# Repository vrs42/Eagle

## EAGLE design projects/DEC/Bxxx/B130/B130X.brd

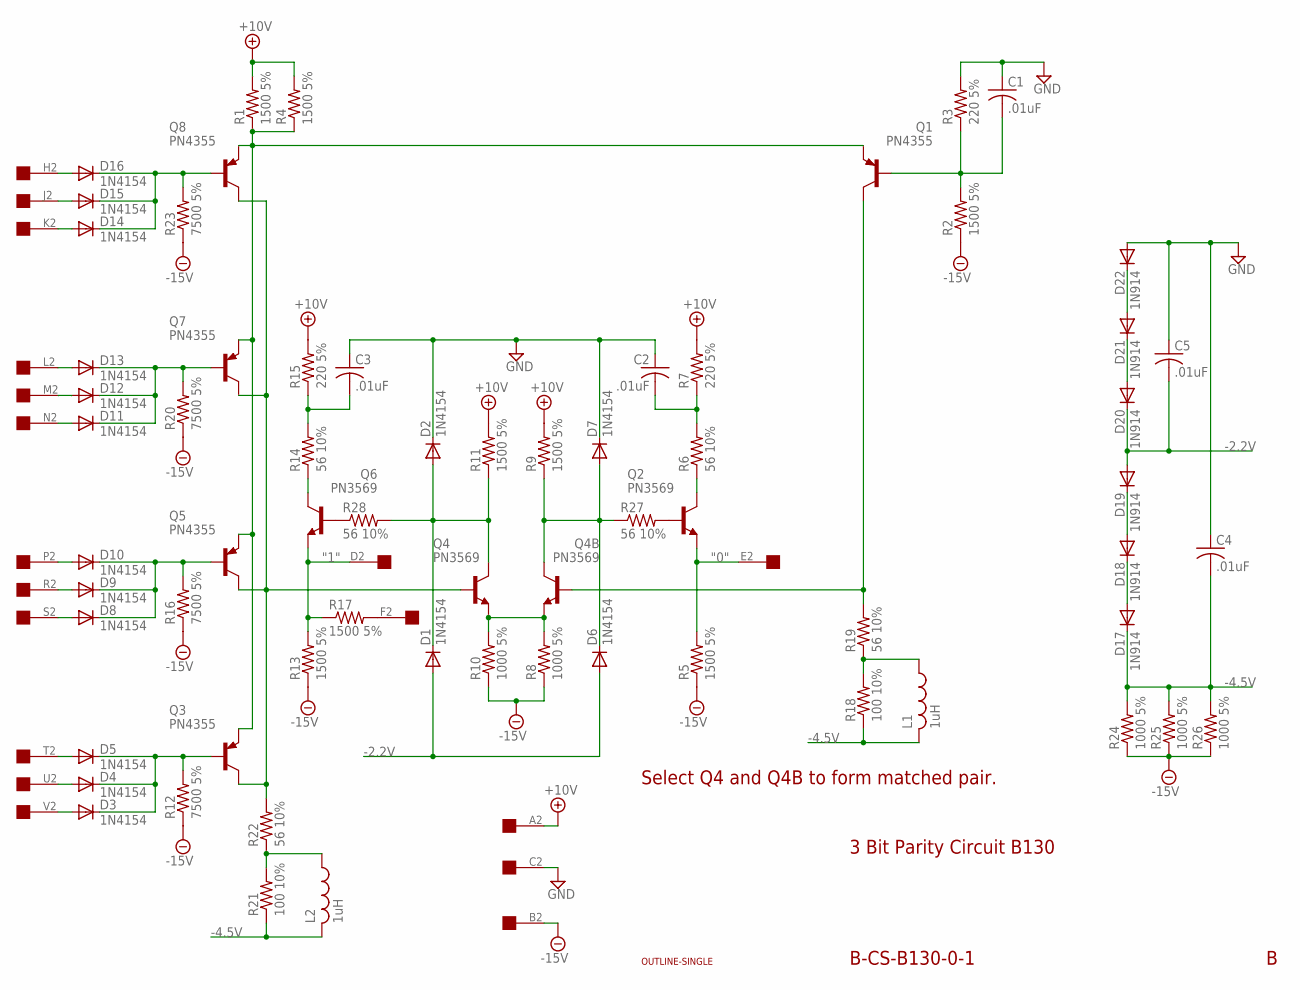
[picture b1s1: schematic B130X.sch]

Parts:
C1, C2, C3, C4, C5: .01uF; C050-025X075
D1, D2, D3, D4, D5, D6, D7, D8, D9, D10, D11, D12, D13, D14, D15, D16: 1N4154; DO35-10
D17, D18, D19, D20, D21, D22: 1N914; DO35-10
L1, L2: 1uH; 0207/10
Q1, Q3, Q5, Q7, Q8: PN4355; TO39
Q2, Q4, Q4B, Q6: PN3569; TO5
R1, R2, R4, R5, R9, R11, R13, R17: 1500 5%; 0207/10
R3, R7, R15: 220 5%; 0207/10
R6, R14, R19, R22, R27, R28: 56 10%; 0207/10
R8, R10, R24, R25, R26: 1000 5%; 0207/10
R12, R16, R20, R23: 7500 5%; 0207/10
R18, R21: 100 10%; 0207/10
U$1: OUTLINE-SINGLE; SINGLE
U$2: EDGE-1; EDGE-CON1

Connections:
"0": Q2.1 (E), R5.2, U$2.E2
"1": Q6.1 (E), R13.2, R17.1, U$2.D2
+10V: R1.2, R4.2, R7.2, R9.2, R11.2, R15.2, U$2.A2
-2.2V: C5.2, D1.A, D6.A, D19.A, D20.C
-4.5V: C4.2, D17.C, L1.2, L2.2, R18.1, R21.1, R24.2, R25.2, R26.2
-15V: R2.1, R5.1, R8.1, R10.1, R12.1, R13.1, R16.1, R20.1, R23.1, R24.1, R25.1, R26.1, U$2.B2
GND: C1.1, C2.1, C3.1, C4.1, C5.1, D2.C, D7.C, D22.A, R3.2, U$2.C2
unnamed: D16.A, U$2.H2
unnamed: D18.A, D19.C
unnamed: D15.A, U$2.J2
unnamed: D17.A, D18.C
unnamed: Q1.1 (E), Q3.1 (E), Q5.1 (E), Q7.1 (E), Q8.1 (E), R1.1, R4.1
unnamed: D14.A, U$2.K2
unnamed: D14.C, D15.C, D16.C, Q8.2 (B), R23.2
unnamed: D13.A, U$2.L2
unnamed: D12.A, U$2.M2
unnamed: L2.1, R21.2, R22.1
unnamed: D11.A, U$2.N2
unnamed: D11.C, D12.C, D13.C, Q7.2 (B), R20.2
unnamed: D10.A, U$2.P2
unnamed: D9.A, U$2.R2
unnamed: D8.A, U$2.S2
unnamed: D8.C, D9.C, D10.C, Q5.2 (B), R16.2
unnamed: D5.A, U$2.T2
unnamed: D4.A, U$2.U2
unnamed: D3.A, U$2.V2
unnamed: D3.C, D4.C, D5.C, Q3.2 (B), R12.2
unnamed: Q3.3 (C), Q4.2 (B), Q5.3 (C), Q7.3 (C), Q8.3 (C), R22.2
unnamed: Q4.1 (E), Q4B.1 (E), R8.2, R10.2
unnamed: D1.C, D2.A, Q4.3 (C), R11.1, R28.2
unnamed: D6.C, D7.A, Q4B.3 (C), R9.1, R27.1
unnamed: Q6.2 (B), R28.1
unnamed: D21.A, D22.C
unnamed: D20.A, D21.C
unnamed: Q2.2 (B), R27.2
unnamed: Q1.3 (C), Q4B.2 (B), R19.2
unnamed: C1.2, Q1.2 (B), R2.2, R3.1
unnamed: R17.2, U$2.F2
unnamed: Q2.3 (C), R6.1
unnamed: Q6.3 (C), R14.1
unnamed: C3.2, R14.2, R15.1
unnamed: C2.2, R6.2, R7.1
unnamed: L1.1, R18.2, R19.1

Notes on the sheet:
3 Bit Parity Circuit B130
B-CS-B130-0-1
Select Q4 and Q4B to form matched pair.

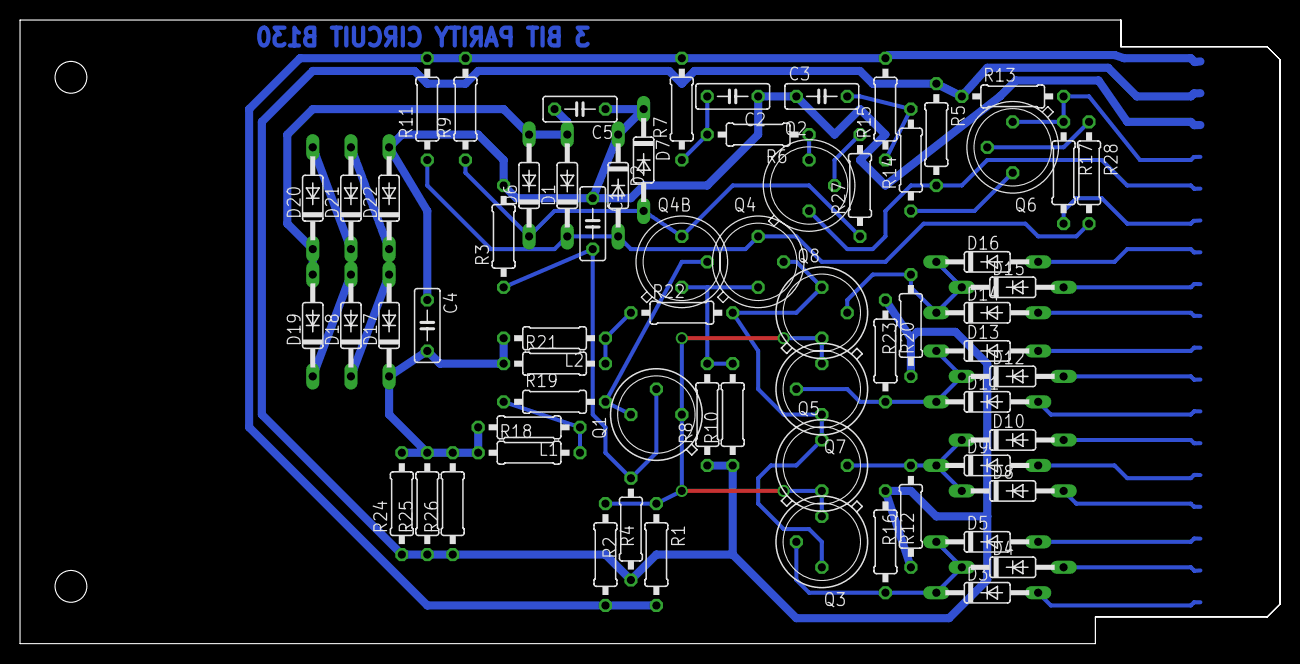
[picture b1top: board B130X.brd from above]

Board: 2 copper layers, 125.7 x 62.2 mm, 68 parts (0 on the bottom side), 43 nets.

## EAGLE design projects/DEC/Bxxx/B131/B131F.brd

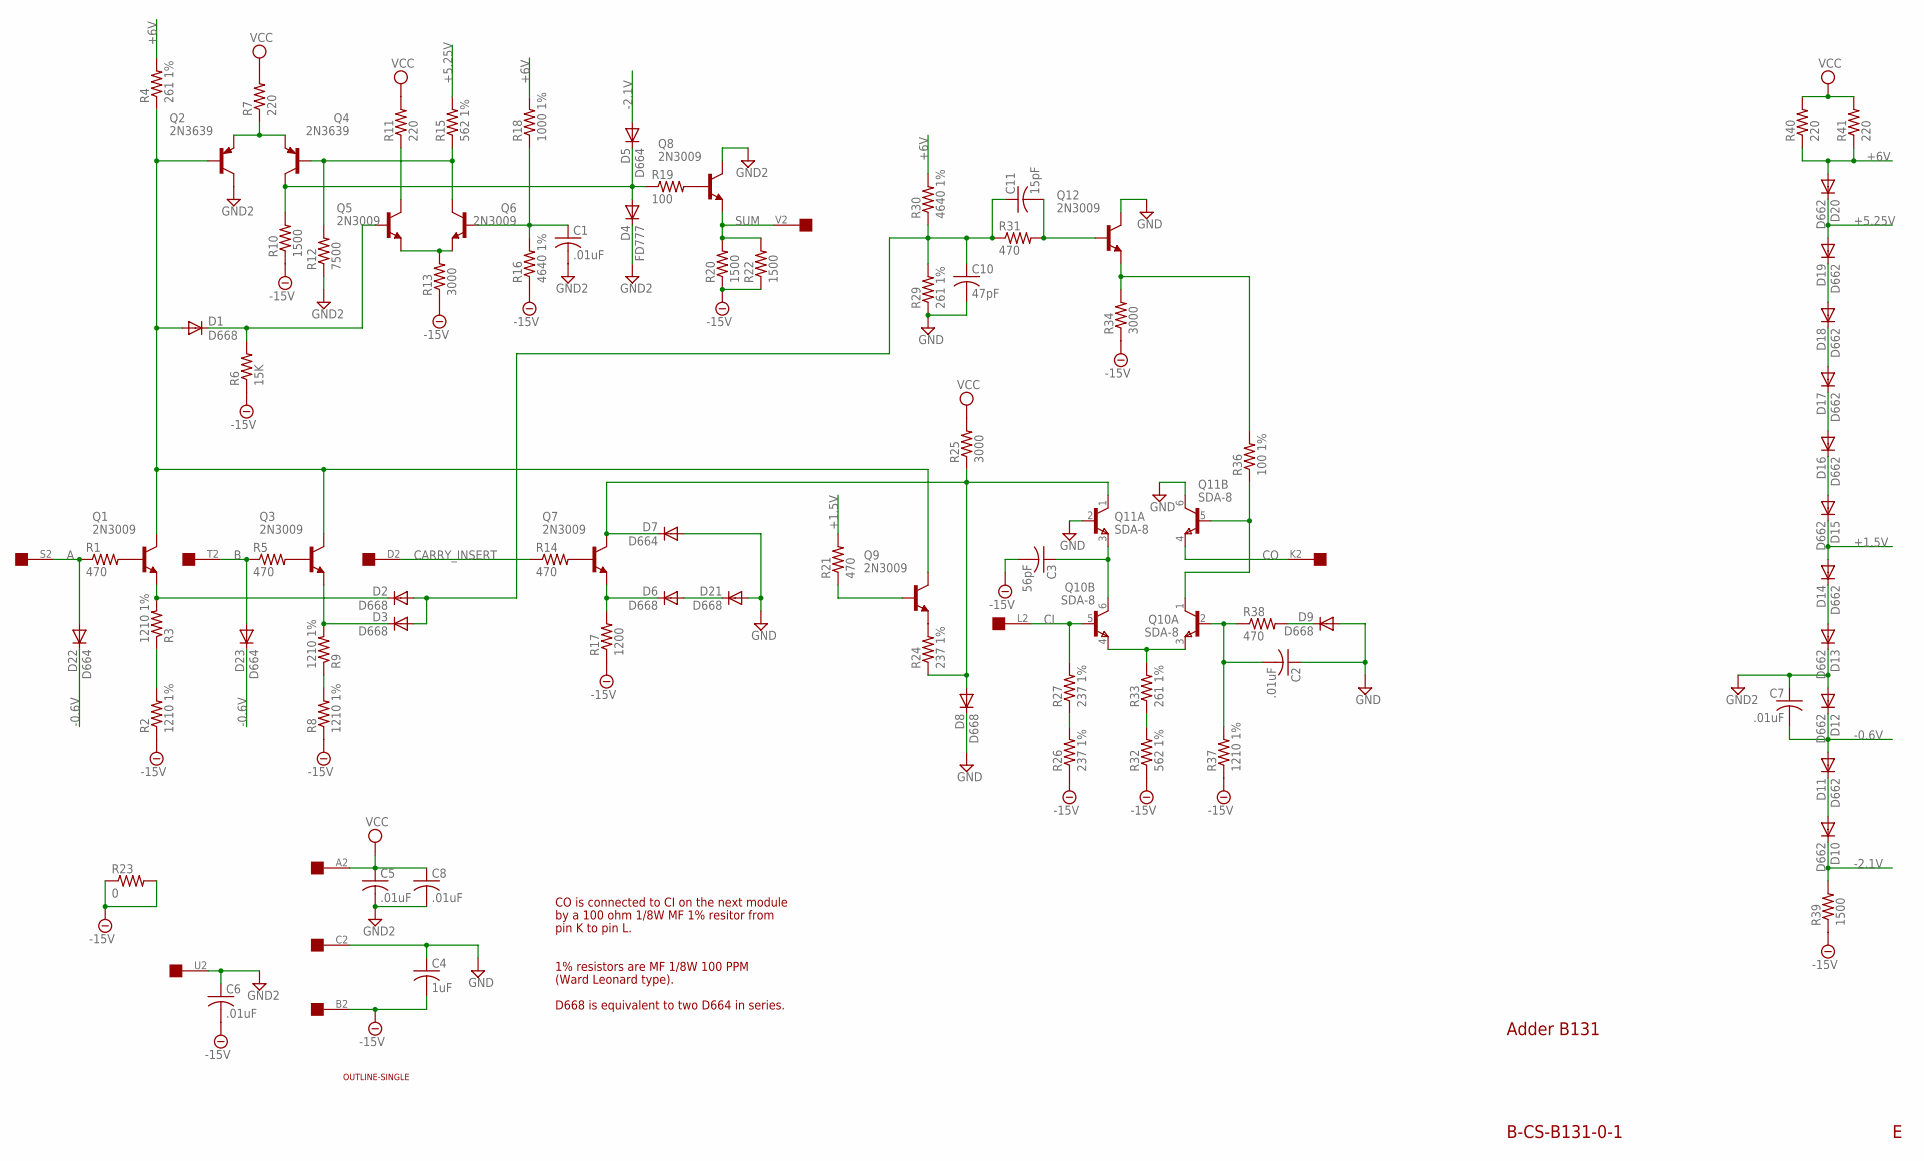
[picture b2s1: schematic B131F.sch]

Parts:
C1, C2, C5, C6, C7, C8: .01uF; C063-025X075
C3: 56pF; C063-025X075
C4: 1uF; C102-043X133
C10: 47pF; C063-025X075
C11: 15pF; C063-025X075
D1, D2, D3, D6, D8, D9, D21: D668; DO35-10
D4: FD777; DO35-10
D5, D7, D22, D23: D664; DO35-10
D10, D11, D12, D13, D14, D15, D16, D17, D18, D19, D20: D662; DO35-10
Q1, Q3, Q5, Q6, Q7, Q8, Q9, Q12: 2N3009; TO5
Q2, Q4: 2N3639; TO5
Q10, Q11: SDA-8; TO78
R1, R5, R14, R21, R31, R38: 470; 0207/10
R2, R3, R8, R9, R37: 1210 1%; 0207/15
R4, R29, R33: 261 1%; 0207/15
R6: 15K; 0207/10
R7, R11, R40, R41: 220; 0207/10
R10, R20, R22, R39: 1500; 0207/10
R12: 7500; 0207/10
R13, R25, R34: 3000; 0207/10
R15, R32: 562 1%; 0207/15
R16, R30: 4640 1%; 0207/15
R17: 1200; 0207/10
R18: 1000 1%; 0207/15
R19: 100; 0207/10
R23: 0; 0207/10
R24, R26, R27: 237 1%; 0207/15
R36: 100 1%; 0207/15
U$1: OUTLINE-SINGLE; SINGLE
U$2: EDGE-1; EDGE-CON1

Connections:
+1.5V: D14.A, D15.C, R21.2
+5.25V: D19.A, D20.C, R15.2
+6V: D20.A, R4.2, R18.2, R30.2, R40.1, R41.1
-0.6V: C7.2, D11.A, D12.C, D22.C, D23.C
-2.1V: D5.A, D10.C, R39.2
-15V: C3.2, C4.2, C6.2, R2.1, R6.1, R8.1, R10.1, R13.1, R16.1, R17.1, R20.1, R22.1, R23.1, R23.2, R26.1, R32.1, R34.1, R37.1, R39.1, U$2.B2
A: D22.A, R1.1, U$2.S2
B: D23.A, R5.1, U$2.T2
CARRY_INSERT: R14.1, U$2.D2
CI: Q10.5 (B), R27.2, U$2.L2
CO: Q11.4 (E), U$2.K2
GND: C2.1, C4.1, C10.2, D7.A, D8.C, D9.A, D21.A, Q11.2 (B), Q11.6 (C), Q12.3 (C), R29.1, U$2.C2
GND2: C1.2, C5.2, C6.1, C7.1, C8.2, D4.C, D12.A, D13.C, Q2.3 (C), Q8.3 (C), R12.1, U$2.U2
unnamed: D1.A, Q1.3 (C), Q2.2 (B), Q3.3 (C), Q9.3 (C), R4.1
unnamed: D2.C, Q1.1 (E), R3.2
unnamed: R2.2, R3.1
unnamed: D3.C, Q3.1 (E), R9.2
unnamed: R8.2, R9.1
unnamed: Q1.2 (B), R1.2
unnamed: Q3.2 (B), R5.2
unnamed: C10.1, C11.1, D2.A, D3.A, R29.2, R30.1, R31.1
unnamed: D6.C, Q7.1 (E), R17.2
unnamed: Q7.2 (B), R14.2
unnamed: D6.A, D21.C
unnamed: D7.C, D8.A, Q7.3 (C), Q11.1 (C), R24.1, R25.1
unnamed: Q9.1 (E), R24.2
unnamed: Q9.2 (B), R21.1
unnamed: Q10.3 (E), Q10.4 (E), R33.2
unnamed: R32.2, R33.1
unnamed: D17.A, D18.C
unnamed: D18.A, D19.C
unnamed: C3.1, Q10.6 (C), Q11.3 (E)
unnamed: D15.A, D16.C
unnamed: D16.A, D17.C
unnamed: D13.A, D14.C
unnamed: Q10.1 (C), Q11.5 (B), R36.1
unnamed: R26.2, R27.1
unnamed: D10.A, D11.C
unnamed: C2.2, Q10.2 (B), R37.2, R38.1
unnamed: D9.C, R38.2
unnamed: Q2.1 (E), Q4.1 (E), R7.1
unnamed: C1.1, Q6.2 (B), R16.2, R18.1
unnamed: Q5.1 (E), Q6.1 (E), R13.2
unnamed: Q5.3 (C), R11.1
unnamed: Q4.2 (B), Q6.3 (C), R12.2, R15.1
unnamed: D4.A, D5.C, Q4.3 (C), R10.2, R19.1
unnamed: D1.C, Q5.2 (B), R6.2
unnamed: Q8.2 (B), R19.2
unnamed: C11.2, Q12.2 (B), R31.2
unnamed: Q12.1 (E), R34.2, R36.2
SUM: Q8.1 (E), R20.2, R22.2, U$2.V2
VCC: C5.1, C8.1, R7.2, R11.2, R25.2, R40.2, R41.2, U$2.A2

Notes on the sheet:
Adder B131
B-CS-B131-0-1
CO is connected to CI on the next module
by a 100 ohm 1/8W MF 1% resitor from
pin K to pin L.
1% resistors are MF 1/8W 100 PPM
(Ward Leonard type).
D668 is equivalent to two D664 in series.

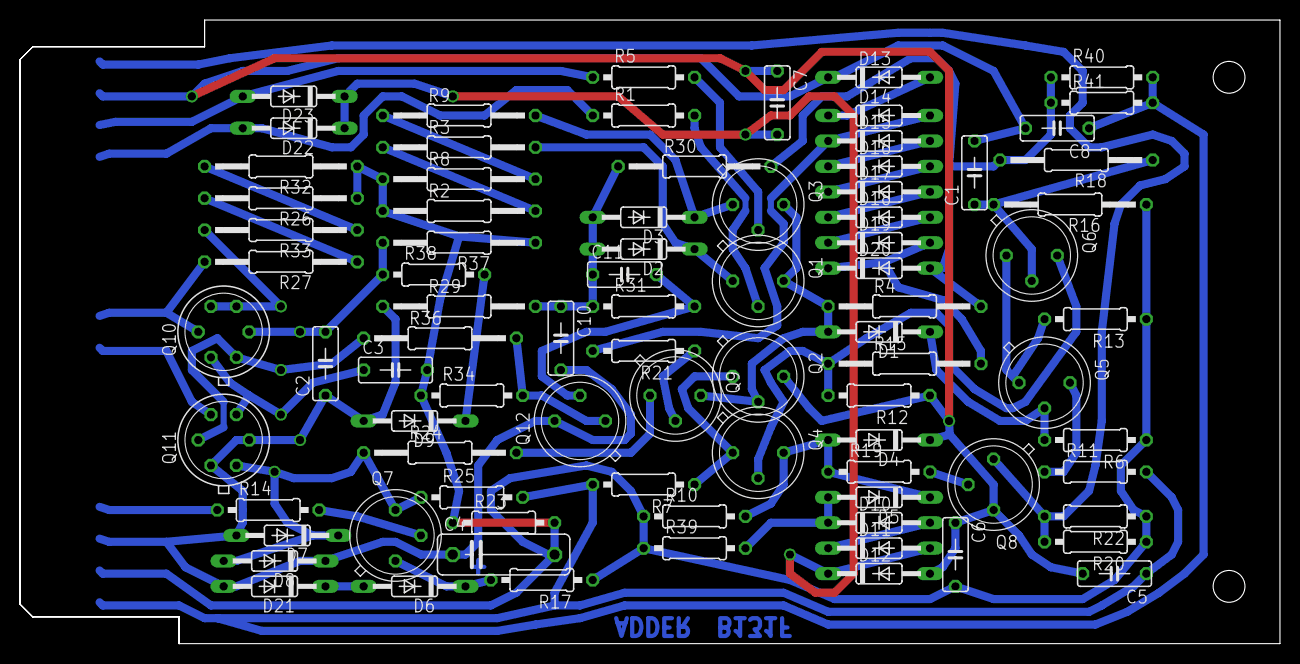
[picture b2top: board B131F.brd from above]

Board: 2 copper layers, 125.7 x 62.2 mm, 86 parts (0 on the bottom side), 52 nets.

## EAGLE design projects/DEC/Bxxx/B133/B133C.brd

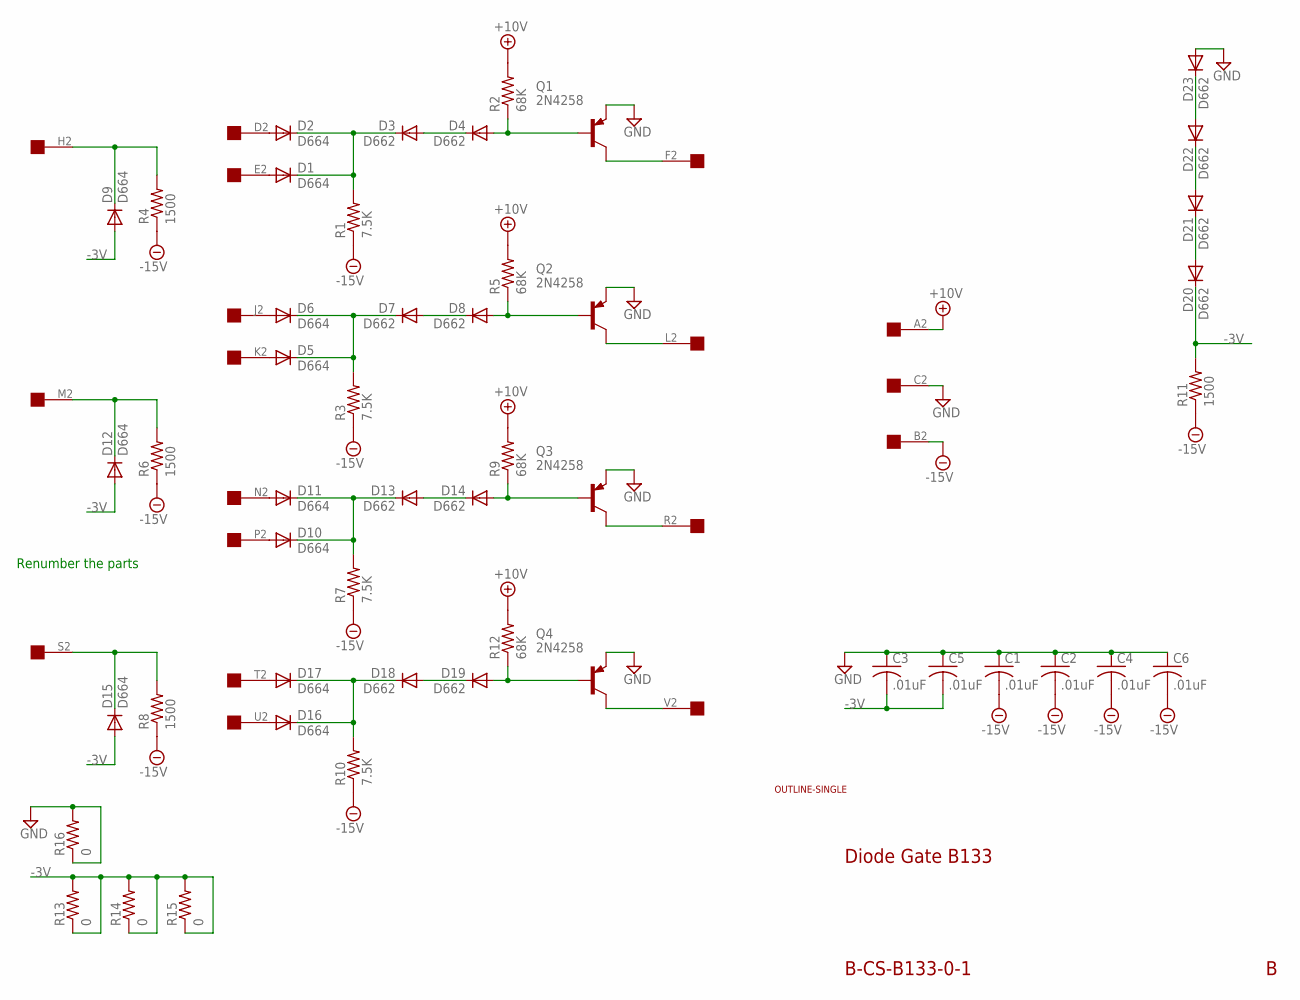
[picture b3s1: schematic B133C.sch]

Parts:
C1, C2, C3, C4, C5, C6: .01uF; C063-025X075
D1, D2, D5, D6, D9, D10, D11, D12, D15, D16, D17: D664; DO35-10
D3, D4, D7, D8, D13, D14, D18, D19, D20, D21, D22, D23: D662; DO35-10
Q1, Q2, Q3, Q4: 2N4258; TO5
R1, R3, R7, R10: 7.5K; 0207/10
R2, R5, R9, R12: 68K; 0207/10
R4, R6, R8, R11: 1500; 0207/10
R13, R14, R15, R16: 0; 0207/10
U$1: OUTLINE-SINGLE; SINGLE
U$2: EDGE-1; EDGE-CON1

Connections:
+10V: R2.2, R5.2, R9.2, R12.2, U$2.A2
-3V: C3.2, C5.2, D9.A, D12.A, D15.A, D20.C, R11.2, R13.1, R13.2, R14.1, R14.2, R15.1, R15.2
-15V: C1.2, C2.2, C4.2, C6.2, R1.1, R3.1, R4.1, R6.1, R7.1, R8.1, R10.1, R11.1, U$2.B2
GND: C1.1, C2.1, C3.1, C4.1, C5.1, C6.1, D23.A, Q1.1 (E), Q2.1 (E), Q3.1 (E), Q4.1 (E), R16.1, R16.2, U$2.C2
unnamed: D5.C, D6.C, D7.C, R3.2
unnamed: D16.C, D17.C, D18.C, R10.2
unnamed: D4.A, Q1.2 (B), R2.1
unnamed: D1.A, U$2.E2
unnamed: D1.C, D2.C, D3.C, R1.2
unnamed: D6.A, U$2.J2
unnamed: D5.A, U$2.K2
unnamed: D18.A, D19.C
unnamed: D7.A, D8.C
unnamed: D2.A, U$2.D2
unnamed: Q1.3 (C), U$2.F2
unnamed: D8.A, Q2.2 (B), R5.1
unnamed: Q2.3 (C), U$2.L2
unnamed: D10.C, D11.C, D13.C, R7.2
unnamed: D3.A, D4.C
unnamed: D11.A, U$2.N2
unnamed: D9.C, R4.2, U$2.H2
unnamed: D10.A, U$2.P2
unnamed: D17.A, U$2.T2
unnamed: D12.C, R6.2, U$2.M2
unnamed: D13.A, D14.C
unnamed: D14.A, Q3.2 (B), R9.1
unnamed: Q3.3 (C), U$2.R2
unnamed: D19.A, Q4.2 (B), R12.1
unnamed: D15.C, R8.2, U$2.S2
unnamed: D22.A, D23.C
unnamed: D21.A, D22.C
unnamed: Q4.3 (C), U$2.V2
unnamed: D20.A, D21.C
unnamed: D16.A, U$2.U2

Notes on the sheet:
Diode Gate B133
B-CS-B133-0-1
Renumber the parts

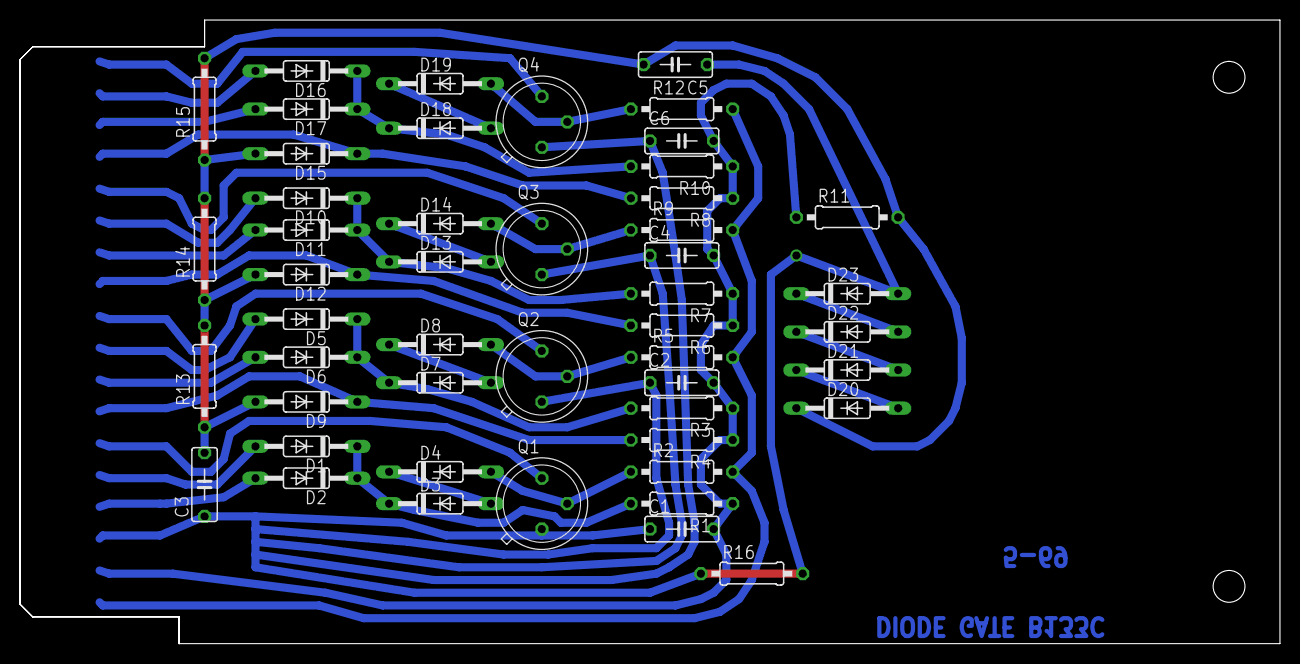
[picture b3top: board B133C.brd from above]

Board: 2 copper layers, 125.7 x 62.2 mm, 51 parts (0 on the bottom side), 34 nets.

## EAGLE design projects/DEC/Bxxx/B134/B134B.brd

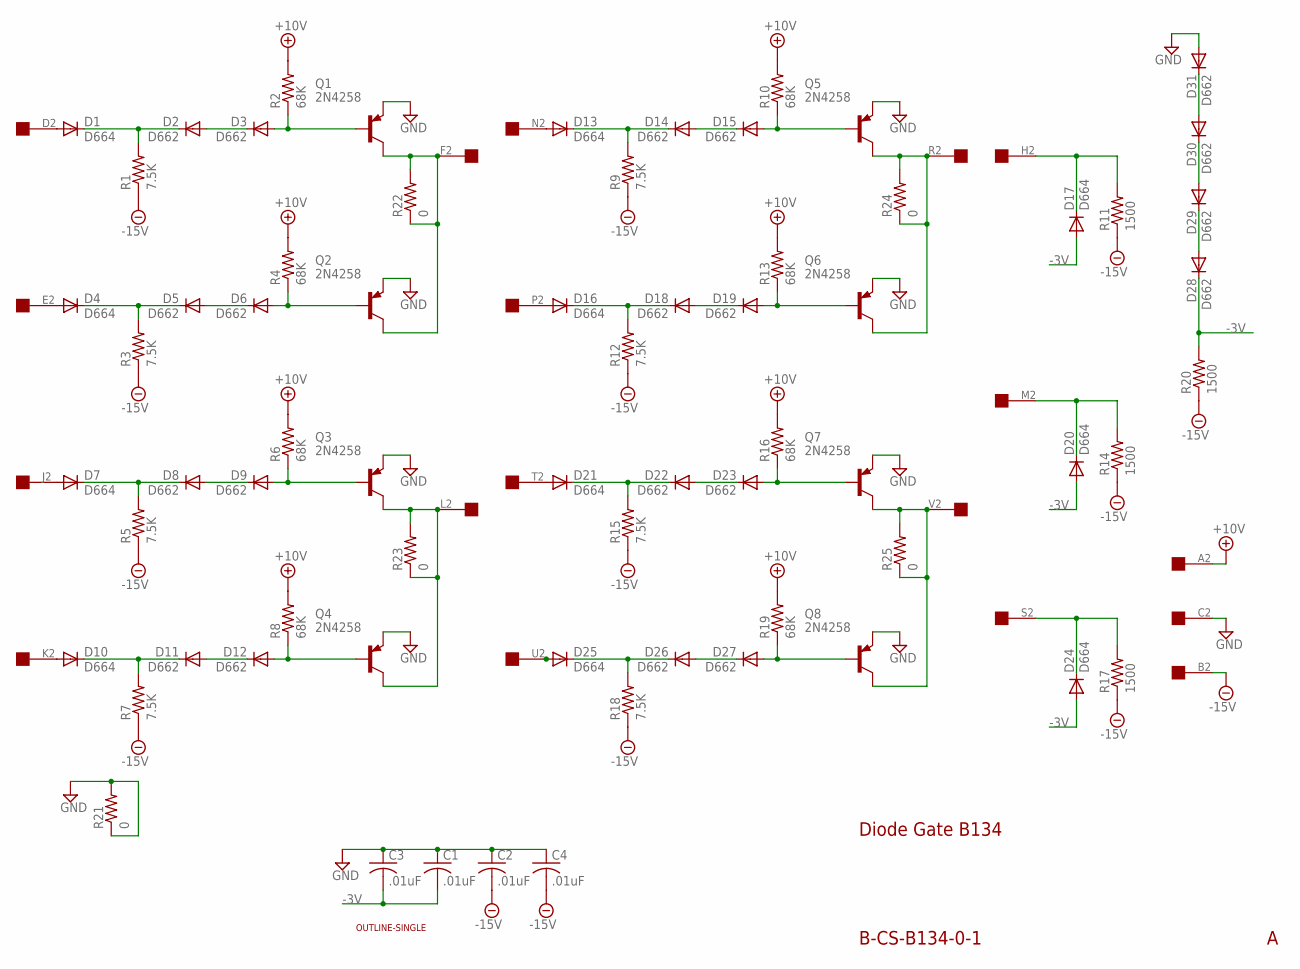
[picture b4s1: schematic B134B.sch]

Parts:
C1, C2, C3, C4: .01uF; C063-025X075
D1, D4, D7, D10, D13, D16, D17, D20, D21, D24, D25: D664; DO35-10
D2, D3, D5, D6, D8, D9, D11, D12, D14, D15, D18, D19, D22, D23, D26, D27, D28, D29, D30, D31: D662; DO35-10
Q1, Q2, Q3, Q4, Q5, Q6, Q7, Q8: 2N4258; TO5
R1, R3, R5, R7, R9, R12, R15, R18: 7.5K; 0207/10
R2, R4, R6, R8, R10, R13, R16, R19: 68K; 0207/10
R11, R14, R17, R20: 1500; 0207/10
R21, R22, R23, R24, R25: 0; 0207/10
U$1: OUTLINE-SINGLE; SINGLE
U$2: EDGE-1; EDGE-CON1

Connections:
+10V: R2.2, R4.2, R6.2, R8.2, R10.2, R13.2, R16.2, R19.2, U$2.A2
-3V: C1.2, C3.2, D17.A, D20.A, D24.A, D28.C, R20.2
-15V: C2.2, C4.2, R1.1, R3.1, R5.1, R7.1, R9.1, R11.1, R12.1, R14.1, R15.1, R17.1, R18.1, R20.1, U$2.B2
GND: C1.1, C2.1, C3.1, C4.1, D31.A, Q1.1 (E), Q2.1 (E), Q3.1 (E), Q4.1 (E), Q5.1 (E), Q6.1 (E), Q7.1 (E), Q8.1 (E), R21.1, R21.2, U$2.C2
unnamed: D4.C, D5.C, R3.2
unnamed: D10.C, D11.C, R7.2
unnamed: D3.A, Q1.2 (B), R2.1
unnamed: D13.C, D14.C, R9.2
unnamed: D1.C, D2.C, R1.2
unnamed: D4.A, U$2.E2
unnamed: D13.A, U$2.N2
unnamed: D11.A, D12.C
unnamed: D5.A, D6.C
unnamed: D1.A, U$2.D2
unnamed: D14.A, D15.C
unnamed: D6.A, Q2.2 (B), R4.1
unnamed: Q1.3 (C), Q2.3 (C), R22.1, R22.2, U$2.F2
unnamed: D7.C, D8.C, R5.2
unnamed: D2.A, D3.C
unnamed: D7.A, U$2.J2
unnamed: D17.C, R11.2, U$2.H2
unnamed: D15.A, Q5.2 (B), R10.1
unnamed: D10.A, U$2.K2
unnamed: D20.C, R14.2, U$2.M2
unnamed: D8.A, D9.C
unnamed: D9.A, Q3.2 (B), R6.1
unnamed: D16.C, D18.C, R12.2
unnamed: D12.A, Q4.2 (B), R8.1
unnamed: D24.C, R17.2, U$2.S2
unnamed: D30.A, D31.C
unnamed: D29.A, D30.C
unnamed: D19.A, Q6.2 (B), R13.1
unnamed: D28.A, D29.C
unnamed: D18.A, D19.C
unnamed: D23.A, Q7.2 (B), R16.1
unnamed: D21.C, D22.C, R15.2
unnamed: D22.A, D23.C
unnamed: D27.A, Q8.2 (B), R19.1
unnamed: D16.A, U$2.P2
unnamed: D21.A, U$2.T2
unnamed: D25.C, D26.C, R18.2
unnamed: D26.A, D27.C
unnamed: Q7.3 (C), Q8.3 (C), R25.1, R25.2, U$2.V2
unnamed: D25.A, U$2.U2
unnamed: Q3.3 (C), Q4.3 (C), R23.1, R23.2, U$2.L2
unnamed: Q5.3 (C), Q6.3 (C), R24.1, R24.2, U$2.R2

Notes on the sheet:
Diode Gate B134
B-CS-B134-0-1

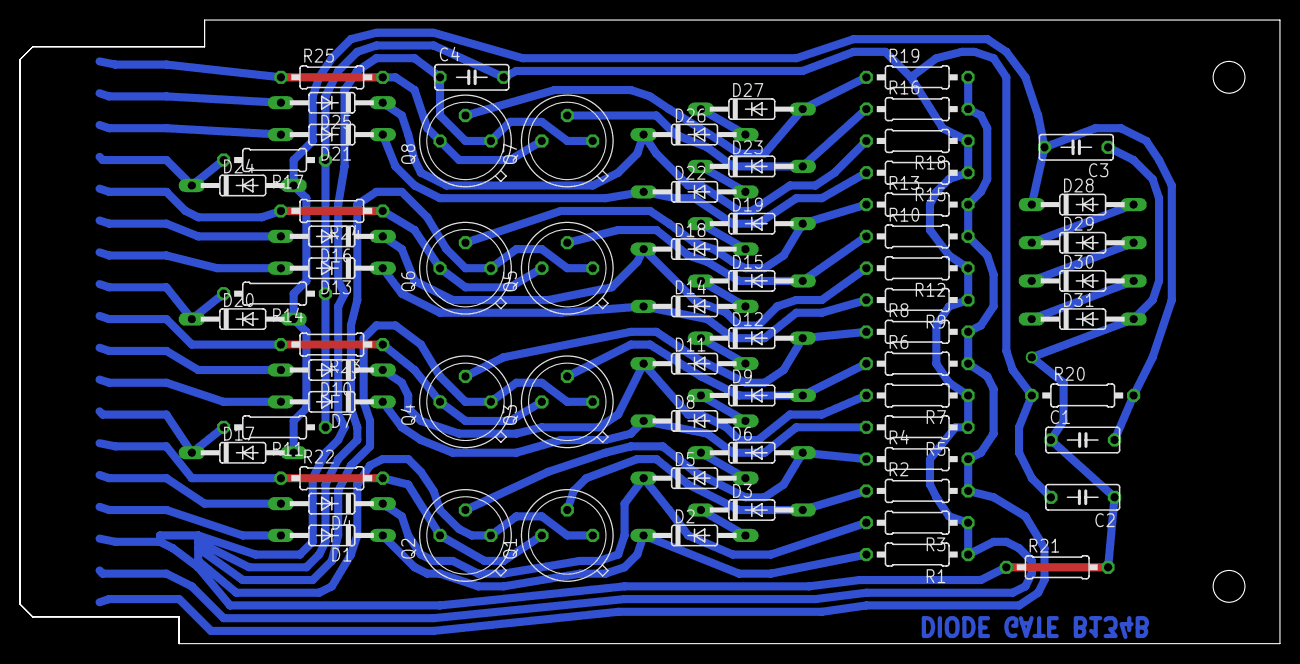
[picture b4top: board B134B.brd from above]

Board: 2 copper layers, 125.7 x 62.2 mm, 70 parts (0 on the bottom side), 46 nets.

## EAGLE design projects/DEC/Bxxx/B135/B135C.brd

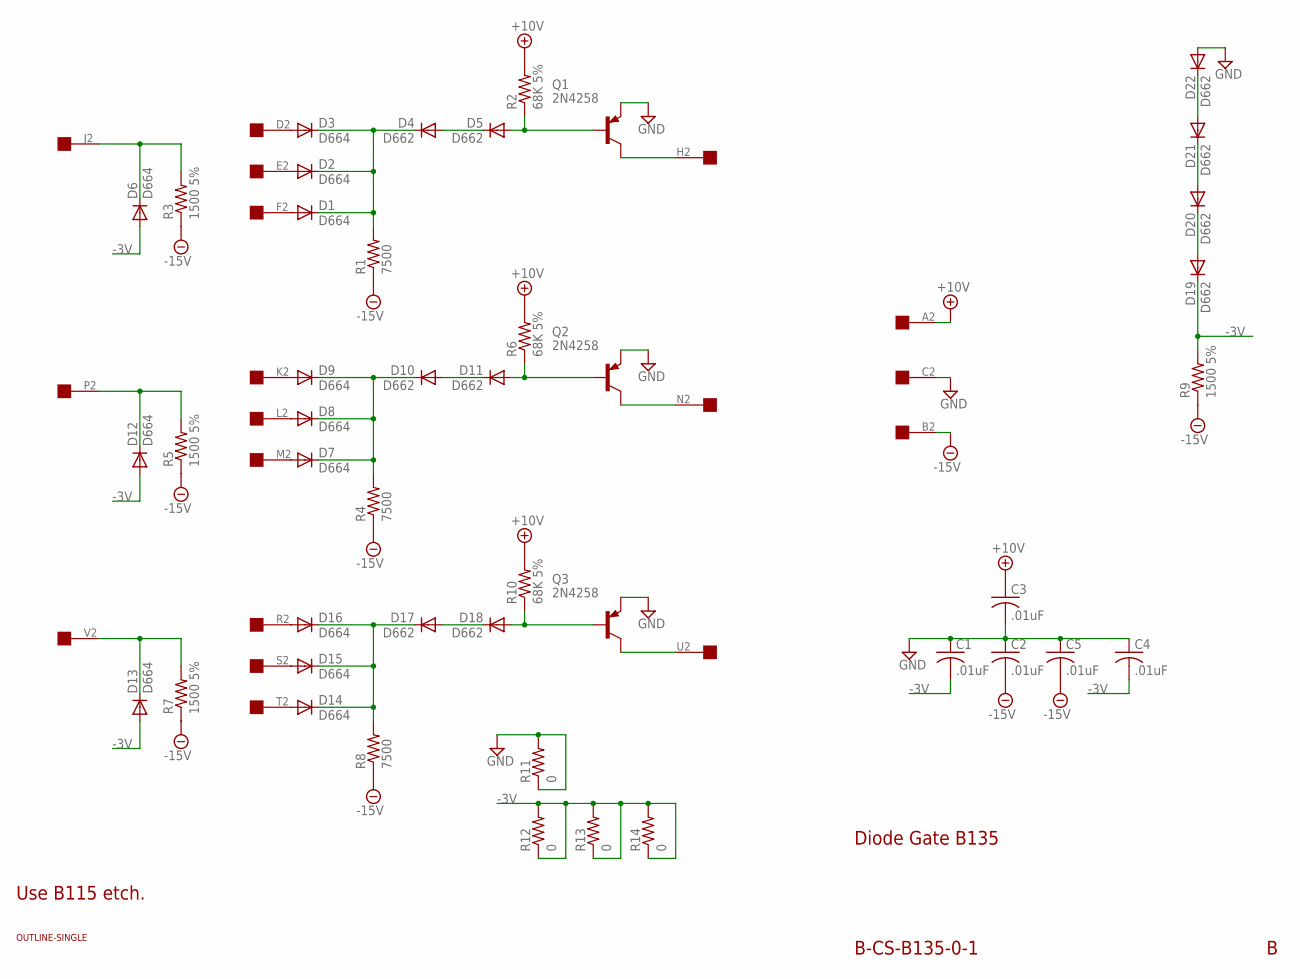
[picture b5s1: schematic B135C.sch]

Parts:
C1, C2, C3, C4, C5: .01uF; C063-025X075
D1, D2, D3, D6, D7, D8, D9, D12, D13, D14, D15, D16: D664; DO35-10
D4, D5, D10, D11, D17, D18, D19, D20, D21, D22: D662; DO35-10
Q1, Q2, Q3: 2N4258; TO5
R1, R4, R8: 7500; 0207/10
R2, R6, R10: 68K 5%; 0207/10
R3, R5, R7, R9: 1500 5%; 0207/10
R11, R12, R13, R14: 0; 0207/10
U$1: OUTLINE-SINGLE; SINGLE
U$2: EDGE-1; EDGE-CON1

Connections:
+10V: C3.1, R2.2, R6.2, R10.2, U$2.A2
-3V: C1.2, C4.2, D6.A, D12.A, D13.A, D19.C, R9.2, R12.1, R12.2, R13.1, R13.2, R14.1, R14.2
-15V: C2.2, C5.2, R1.1, R3.1, R4.1, R5.1, R7.1, R8.1, R9.1, U$2.B2
GND: C1.1, C2.1, C3.2, C4.1, C5.1, D22.A, Q1.1 (E), Q2.1 (E), Q3.1 (E), R11.1, R11.2, U$2.C2
unnamed: D7.C, D8.C, D9.C, D10.C, R4.2
unnamed: D1.A, U$2.F2
unnamed: D5.A, Q1.2 (B), R2.1
unnamed: D2.A, U$2.E2
unnamed: D1.C, D2.C, D3.C, D4.C, R1.2
unnamed: D9.A, U$2.K2
unnamed: D8.A, U$2.L2
unnamed: D7.A, U$2.M2
unnamed: D10.A, D11.C
unnamed: D3.A, U$2.D2
unnamed: Q1.3 (C), U$2.H2
unnamed: D11.A, Q2.2 (B), R6.1
unnamed: Q2.3 (C), U$2.N2
unnamed: D14.C, D15.C, D16.C, D17.C, R8.2
unnamed: D4.A, D5.C
unnamed: D16.A, U$2.R2
unnamed: D6.C, R3.2, U$2.J2
unnamed: D15.A, U$2.S2
unnamed: D14.A, U$2.T2
unnamed: D12.C, R5.2, U$2.P2
unnamed: D17.A, D18.C
unnamed: D18.A, Q3.2 (B), R10.1
unnamed: Q3.3 (C), U$2.U2
unnamed: D13.C, R7.2, U$2.V2
unnamed: D21.A, D22.C
unnamed: D20.A, D21.C
unnamed: D19.A, D20.C

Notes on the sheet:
Diode Gate B135
B-CS-B135-0-1
Use B115 etch.

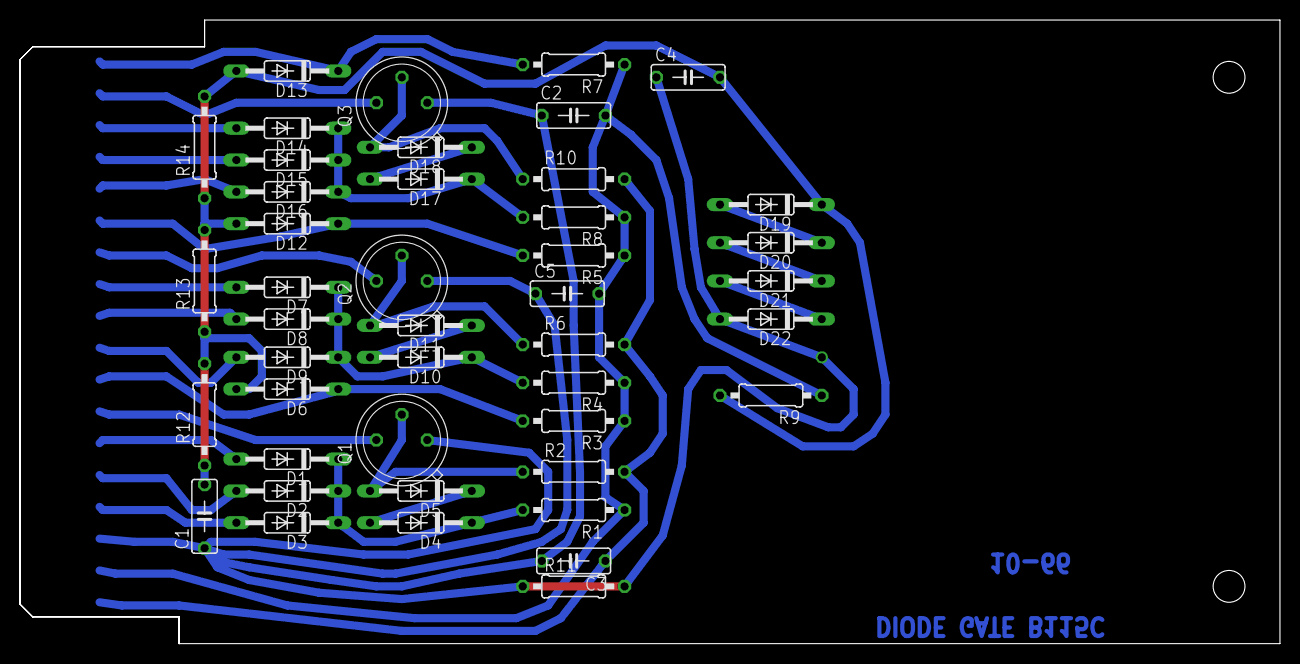
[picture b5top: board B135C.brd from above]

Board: 2 copper layers, 125.7 x 62.2 mm, 46 parts (0 on the bottom side), 31 nets.
